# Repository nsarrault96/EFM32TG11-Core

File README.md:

# Kicad Project Template

This is a simple kicad project template designed to use submodules for any additional pieces including libraries,
firmware/software and CAD design.

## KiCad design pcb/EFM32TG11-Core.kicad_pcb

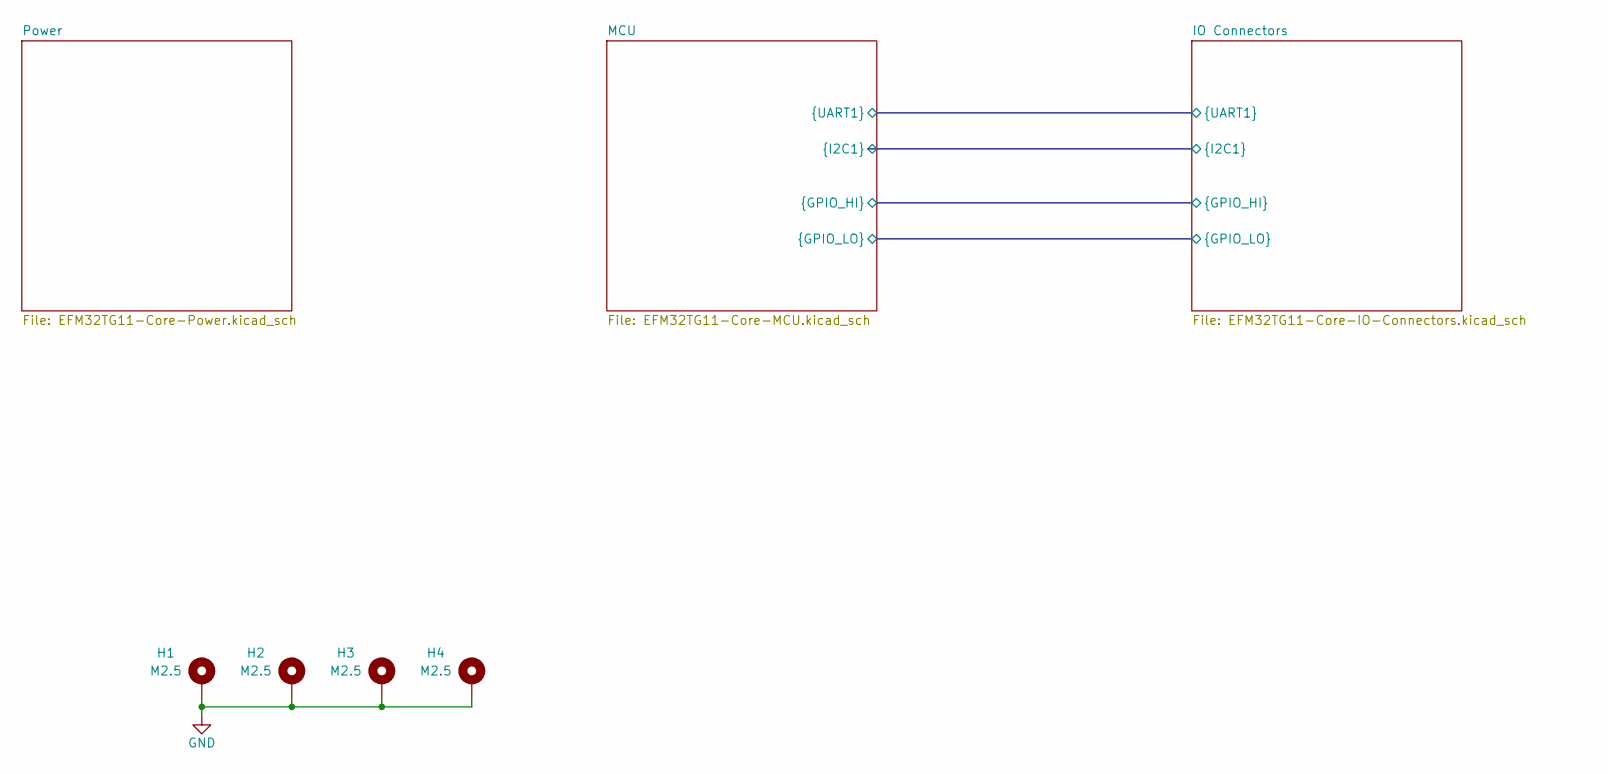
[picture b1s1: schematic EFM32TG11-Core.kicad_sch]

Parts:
H1, H2, H3, H4: M2.5; MountingHole_2.7mm_M2.5_Pad

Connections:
GND: H1.1, H2.1, H3.1, H4.1; also elsewhere on the board

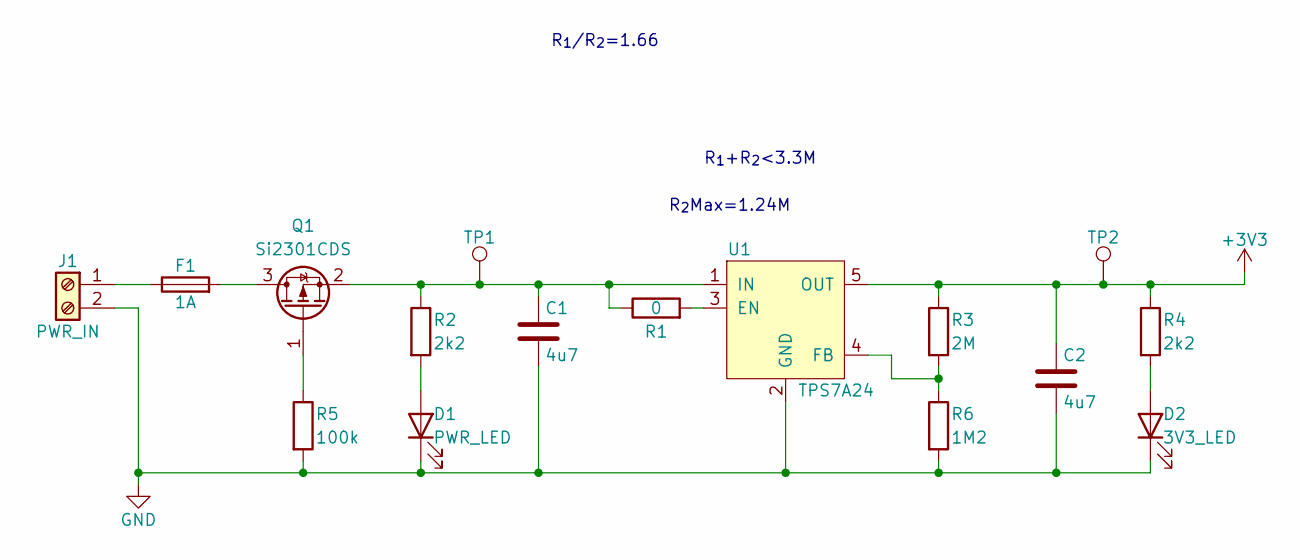
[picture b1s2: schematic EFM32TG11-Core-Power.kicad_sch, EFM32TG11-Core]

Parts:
C1, C2: 4u7; C_0805_2012Metric; PartsBox PN CAP-0805-4u7-X7R-25V
D1: PWR_LED; D_0603_1608Metric_Pad1.05x0.95mm_HandSolder; PartsBox PN LTST-C191KRKT
D2: 3V3_LED; D_0603_1608Metric_Pad1.05x0.95mm_HandSolder; PartsBox PN LTST-C191KRKT
F1: 1A; Fuse_0603_1608Metric; PartsBox PN 0686F1000-01
J1: PWR_IN; TerminalBlock_Phoenix_PT-1,5-2-3.5-H_1x02_P3.50mm_Horizontal; PartsBox PN 1984617
Q1: Si2301CDS; SOT-23; PartsBox PN SI2301CDS-T1-GE3
R1: 0; R_0603_1608Metric; PartsBox PN RES-0603-0R-0.1W
R2, R4: 2k2; R_0603_1608Metric; PartsBox PN RES-0603-2k2-0.1W
R3: 2M; R_0603_1608Metric; PartsBox PN RES-0603-2M-0.1W
R5: 100k; R_0603_1608Metric; PartsBox PN RES-0603-100k-0.1W
R6: 1M2; R_0603_1608Metric; PartsBox PN RES-0603-1M2-0.1W
TP1, TP2: TestPoint; TestPoint_Pad_D1.0mm
U1: TPS7A24; SOT-23-5; PartsBox PN TPS7A2401DBVR

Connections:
+3V3: C2.1, R3.1, R4.1, TP2.1, U1.5 (OUT); also elsewhere on the board
GND: C1.2, C2.2, D1.1 (K), D2.1 (K), J1.2, R5.2, R6.2, U1.2 (GND); also elsewhere on the board
unnamed: C1.1, Q1.2 (S), R1.1, R2.1, TP1.1, U1.1 (IN)
unnamed: D1.2 (A), R2.2
unnamed: D2.2 (A), R4.2
unnamed: F1.1, J1.1
unnamed: F1.2, Q1.3 (D)
unnamed: Q1.1 (G), R5.1
unnamed: R1.2, U1.3 (EN)
unnamed: R3.2, R6.1, U1.4 (FB)

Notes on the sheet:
R_{2}Max=1.24M
R_{1}/R_{2}=1.66
R_{1}+R_{2}<3.3M

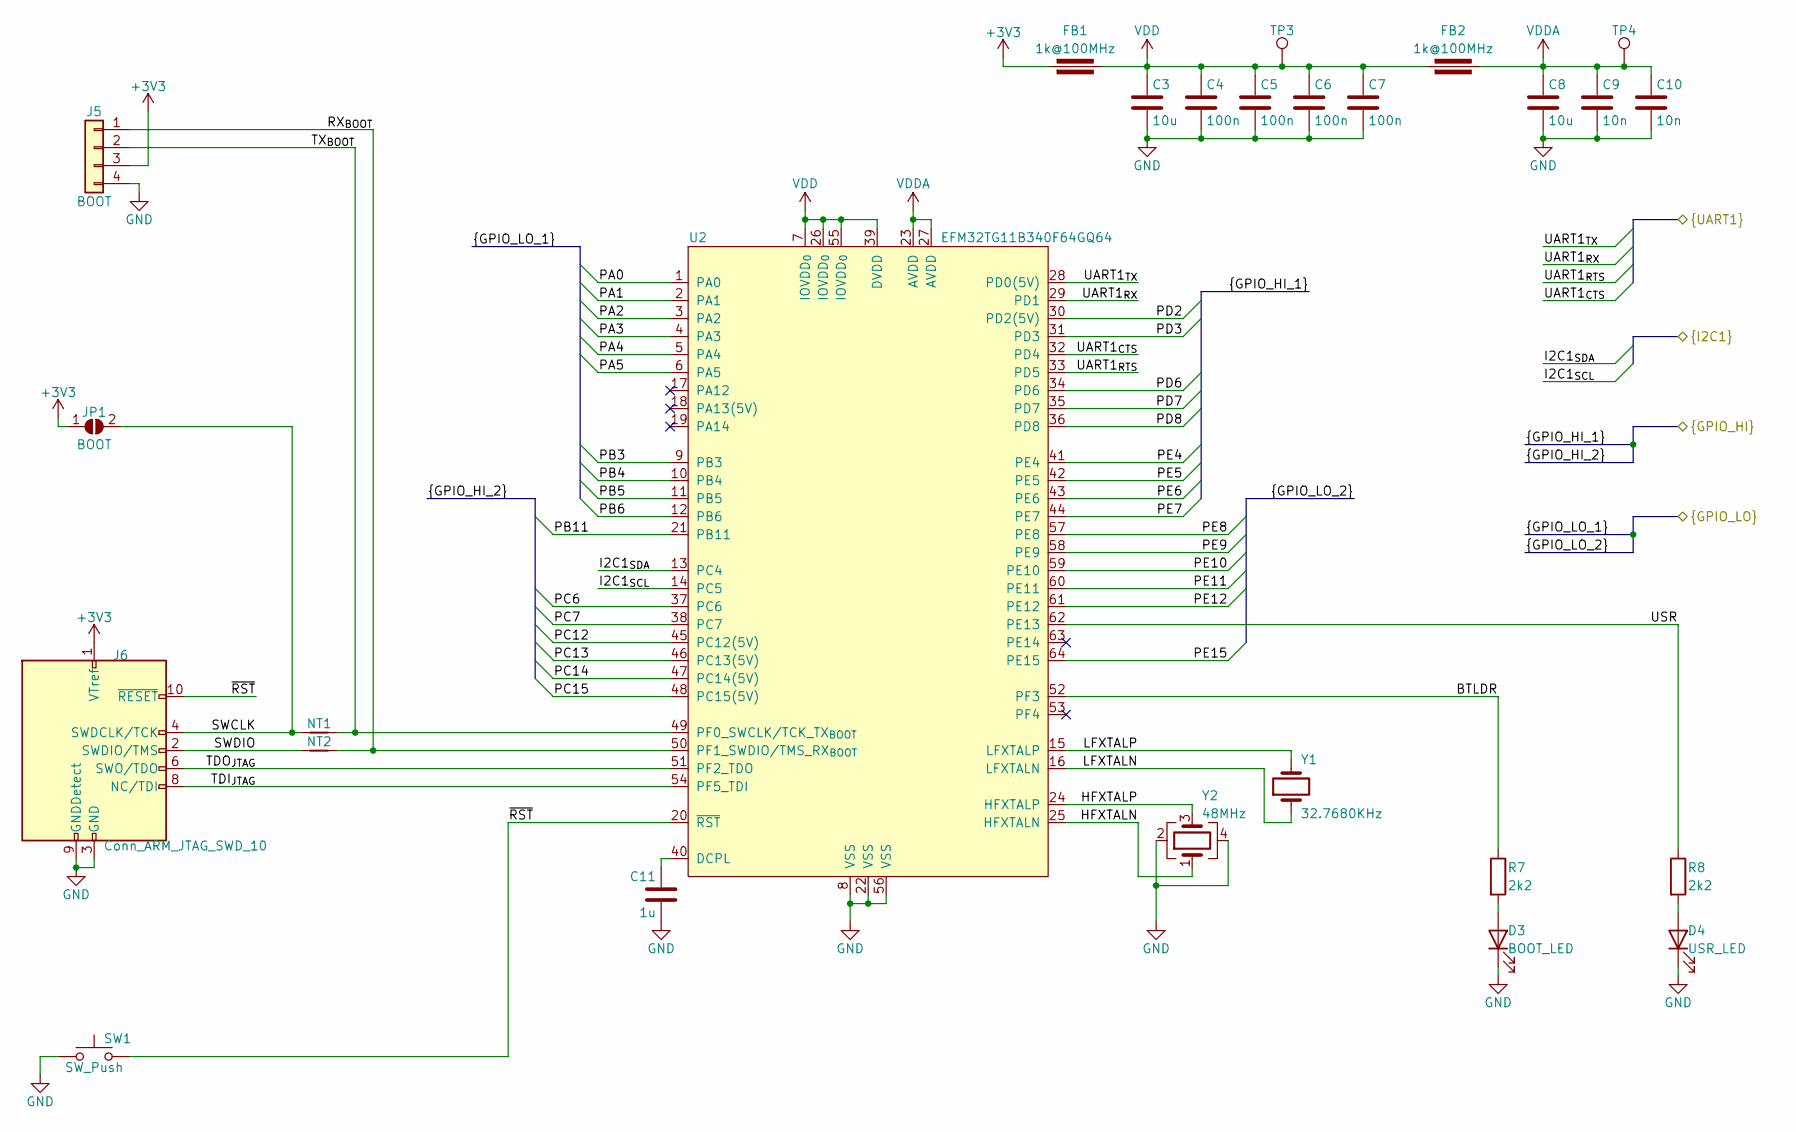
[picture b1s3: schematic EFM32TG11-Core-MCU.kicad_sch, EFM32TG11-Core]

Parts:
C3, C8: 10u; C_1206_3216Metric; PartsBox PN CAP-1206-10u-X7R-25V
C4, C5, C6, C7: 100n; C_0603_1608Metric; PartsBox PN CAP-0603-100n-X7R-50V
C9, C10: 10n; C_0603_1608Metric; PartsBox PN CAP-0603-10n-X7R-50V
C11: 1u; C_0603_1608Metric; PartsBox PN CAP-0603-1u-X7R-25V
D3: BOOT_LED; D_0603_1608Metric_Pad1.05x0.95mm_HandSolder; PartsBox PN LTST-C191KFKT
D4: USR_LED; D_0603_1608Metric_Pad1.05x0.95mm_HandSolder; PartsBox PN LTST-C191KFKT
FB1, FB2: 1k@100MHz; L_0603_1608Metric; PartsBox PN BLM18KG102SN1D
J5: BOOT; PinHeader_1x04_P2.54mm_Horizontal
J6: Conn_ARM_JTAG_SWD_10; PinHeader_2x05_P1.27mm_Vertical
JP1: BOOT; SolderJumper-2_P1.3mm_Open_RoundedPad1.0x1.5mm
NT1, NT2: NetTie_2; NetTie-2_THT_Pad0.3mm
R7, R8: 2k2; R_0603_1608Metric; PartsBox PN RES-0603-2k2-0.1W
SW1: SW_Push; SW_SPST_CK_RS282G05A3; PartsBox PN TS-1101-C-W
TP3, TP4: TestPoint; TestPoint_Pad_D1.0mm
U2: EFM32TG11B340F64GQ64; TQFP-64_10x10mm_P0.5mm; PartsBox PN EFM32TG11B340F64GQ64-A
Y1: 32.7680KHz; Crystal_SMD_MicroCrystal_CC7V-T1A-2Pin_3.2x1.5mm; PartsBox PN FC-135 32.7680KA-AG5
Y2: 48MHz; Crystal_SMD_2016-4Pin_2.0x1.6mm; PartsBox PN 7D048000I01

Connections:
+3V3: FB1.1, J5.3, J6.1 (VTref), JP1.1 (A); also elsewhere on the board
/IO Connectors/UART1_{CTS}: U2.32 (PD4); also elsewhere on the board
/IO Connectors/UART1_{RTS}: U2.33 (PD5); also elsewhere on the board
/IO Connectors/UART1_{RX}: U2.29 (PD1); also elsewhere on the board
/IO Connectors/UART1_{TX}: U2.28 (PD0(5V)); also elsewhere on the board
/MCU/BTLDR: R7.1, U2.52 (PF3)
/MCU/HFXTALN: U2.25 (HFXTALN), Y2.1
/MCU/HFXTALP: U2.24 (HFXTALP), Y2.3
/MCU/I2C1_{SCL}: U2.14 (PC5)
/MCU/I2C1_{SDA}: U2.13 (PC4)
/MCU/LFXTALN: U2.16 (LFXTALN), Y1.1
/MCU/LFXTALP: U2.15 (LFXTALP), Y1.2
/MCU/PA0: U2.1 (PA0)
/MCU/PA1: U2.2 (PA1)
/MCU/PA2: U2.3 (PA2)
/MCU/PA3: U2.4 (PA3)
/MCU/PA4: U2.5 (PA4)
/MCU/PA5: U2.6 (PA5)
/MCU/PB3: U2.9 (PB3)
/MCU/PB4: U2.10 (PB4)
/MCU/PB5: U2.11 (PB5)
/MCU/PB6: U2.12 (PB6)
/MCU/PB11: U2.21 (PB11)
/MCU/PC6: U2.37 (PC6)
/MCU/PC7: U2.38 (PC7)
/MCU/PC12: U2.45 (PC12(5V))
/MCU/PC13: U2.46 (PC13(5V))
/MCU/PC14: U2.47 (PC14(5V))
/MCU/PC15: U2.48 (PC15(5V))
/MCU/PD2: U2.30 (PD2(5V))
/MCU/PD3: U2.31 (PD3)
/MCU/PD6: U2.34 (PD6)
/MCU/PD7: U2.35 (PD7)
/MCU/PD8: U2.36 (PD8)
/MCU/PE4: U2.41 (PE4)
/MCU/PE5: U2.42 (PE5)
/MCU/PE6: U2.43 (PE6)
/MCU/PE7: U2.44 (PE7)
/MCU/PE8: U2.57 (PE8)
/MCU/PE9: U2.58 (PE9)
/MCU/PE10: U2.59 (PE10)
/MCU/PE11: U2.60 (PE11)
/MCU/PE12: U2.61 (PE12)
/MCU/PE15: U2.64 (PE15)
/MCU/RX_{BOOT}: J5.1, NT2.2, U2.50 (PF1_SWDIO/TMS_RX_{BOOT})
/MCU/SWCLK: J6.4 (SWDCLK/TCK), JP1.2 (B), NT1.1
/MCU/SWDIO: J6.2 (SWDIO/TMS), NT2.1
/MCU/TDI_{JTAG}: J6.8 (NC/TDI), U2.54 (PF5_TDI)
/MCU/TDO_{JTAG}: J6.6 (SWO/TDO), U2.51 (PF2_TDO)
/MCU/TX_{BOOT}: J5.2, NT1.2, U2.49 (PF0_SWCLK/TCK_TX_{BOOT})
/MCU/USR: R8.1, U2.62 (PE13)
/MCU/~RST: J6.10 (~RESET), SW1.2, U2.20 (~RST)
GND: C3.2, C4.2, C5.2, C6.2, C7.2, C8.2, C9.2, C10.2, C11.2, D3.1 (K), D4.1 (K), J5.4, J6.3 (GND), J6.5 (GND), J6.9 (GNDDetect), SW1.1, U2.8 (VSS), U2.22 (VSS), U2.56 (VSS), Y2.2, Y2.4; also elsewhere on the board
unnamed: C11.1, U2.40 (DCPL)
unnamed: D3.2 (A), R7.2
unnamed: D4.2 (A), R8.2
VDD: C3.1, C4.1, C5.1, C6.1, C7.1, FB1.2, FB2.1, TP3.1, U2.7 (IOVDD_{0}), U2.26 (IOVDD_{0}), U2.39 (DVDD), U2.55 (IOVDD_{0})
VDDA: C8.1, C9.1, C10.1, FB2.2, TP4.1, U2.23 (AVDD), U2.27 (AVDD)

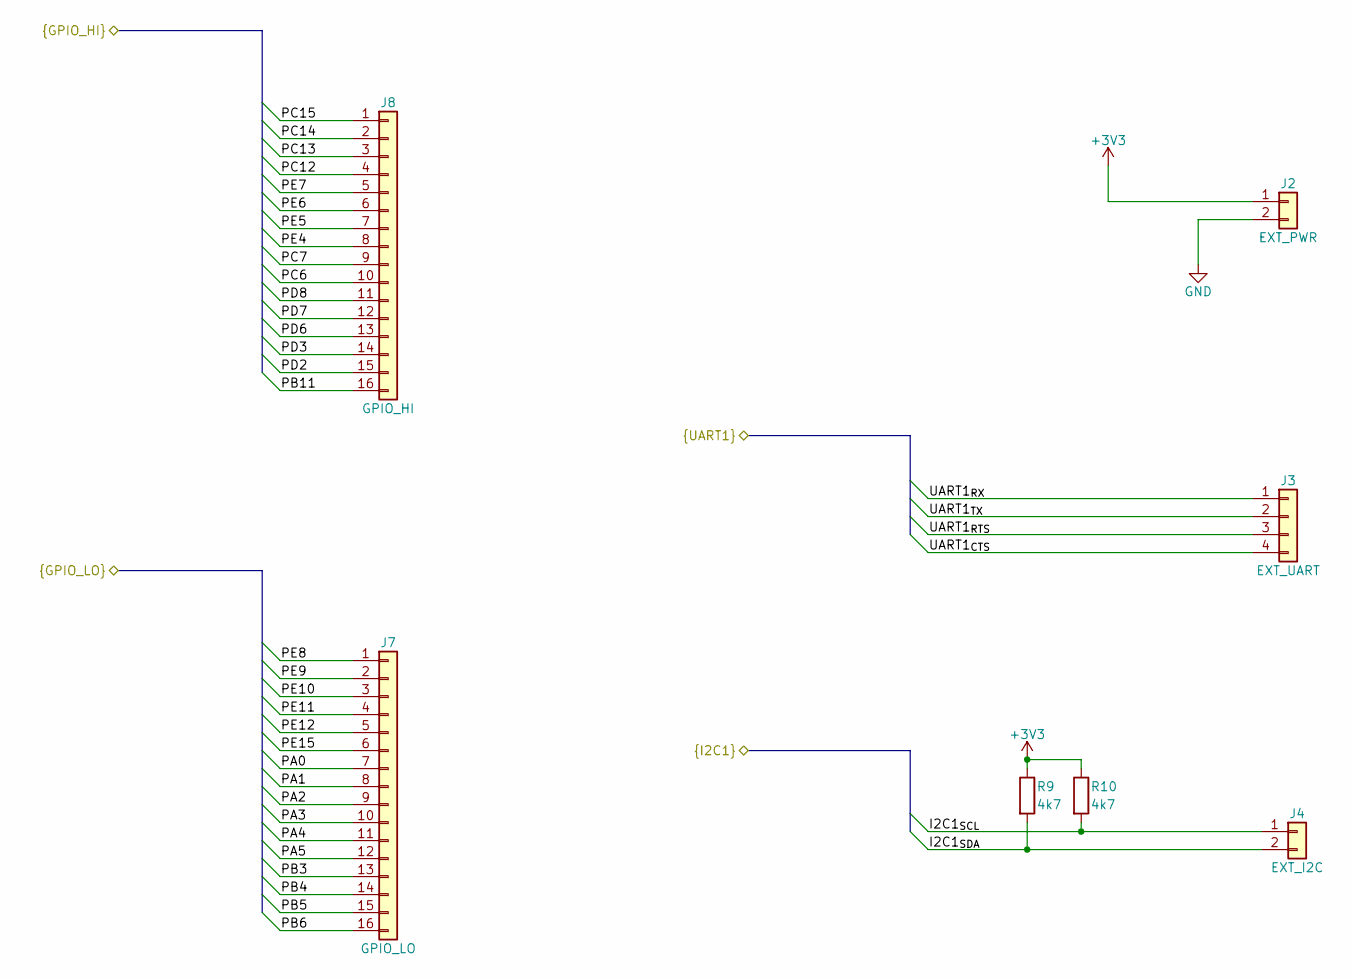
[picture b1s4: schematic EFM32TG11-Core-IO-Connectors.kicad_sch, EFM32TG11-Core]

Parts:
J2: EXT_PWR; PinHeader_1x02_P2.54mm_Horizontal
J3: EXT_UART; PinHeader_1x04_P2.54mm_Horizontal
J4: EXT_I2C; PinHeader_1x02_P2.54mm_Horizontal
J7: GPIO_LO; PinSocket_1x16_P2.54mm_Vertical
J8: GPIO_HI; PinSocket_1x16_P2.54mm_Vertical
R9, R10: 4k7; R_0603_1608Metric; PartsBox PN RES-0603-4k7-0.1W

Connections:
+3V3: J2.1, R9.1, R10.1; also elsewhere on the board
/IO Connectors/I2C1_{SCL}: J4.1, R10.2
/IO Connectors/I2C1_{SDA}: J4.2, R9.2
/IO Connectors/PA0: J7.7
/IO Connectors/PA1: J7.8
/IO Connectors/PA2: J7.9
/IO Connectors/PA3: J7.10
/IO Connectors/PA4: J7.11
/IO Connectors/PA5: J7.12
/IO Connectors/PB3: J7.13
/IO Connectors/PB4: J7.14
/IO Connectors/PB5: J7.15
/IO Connectors/PB6: J7.16
/IO Connectors/PB11: J8.16
/IO Connectors/PC6: J8.10
/IO Connectors/PC7: J8.9
/IO Connectors/PC12: J8.4
/IO Connectors/PC13: J8.3
/IO Connectors/PC14: J8.2
/IO Connectors/PC15: J8.1
/IO Connectors/PD2: J8.15
/IO Connectors/PD3: J8.14
/IO Connectors/PD6: J8.13
/IO Connectors/PD7: J8.12
/IO Connectors/PD8: J8.11
/IO Connectors/PE4: J8.8
/IO Connectors/PE5: J8.7
/IO Connectors/PE6: J8.6
/IO Connectors/PE7: J8.5
/IO Connectors/PE8: J7.1
/IO Connectors/PE9: J7.2
/IO Connectors/PE10: J7.3
/IO Connectors/PE11: J7.4
/IO Connectors/PE12: J7.5
/IO Connectors/PE15: J7.6
/IO Connectors/UART1_{CTS}: J3.4; also elsewhere on the board
/IO Connectors/UART1_{RTS}: J3.3; also elsewhere on the board
/IO Connectors/UART1_{RX}: J3.1; also elsewhere on the board
/IO Connectors/UART1_{TX}: J3.2; also elsewhere on the board
GND: J2.2; also elsewhere on the board

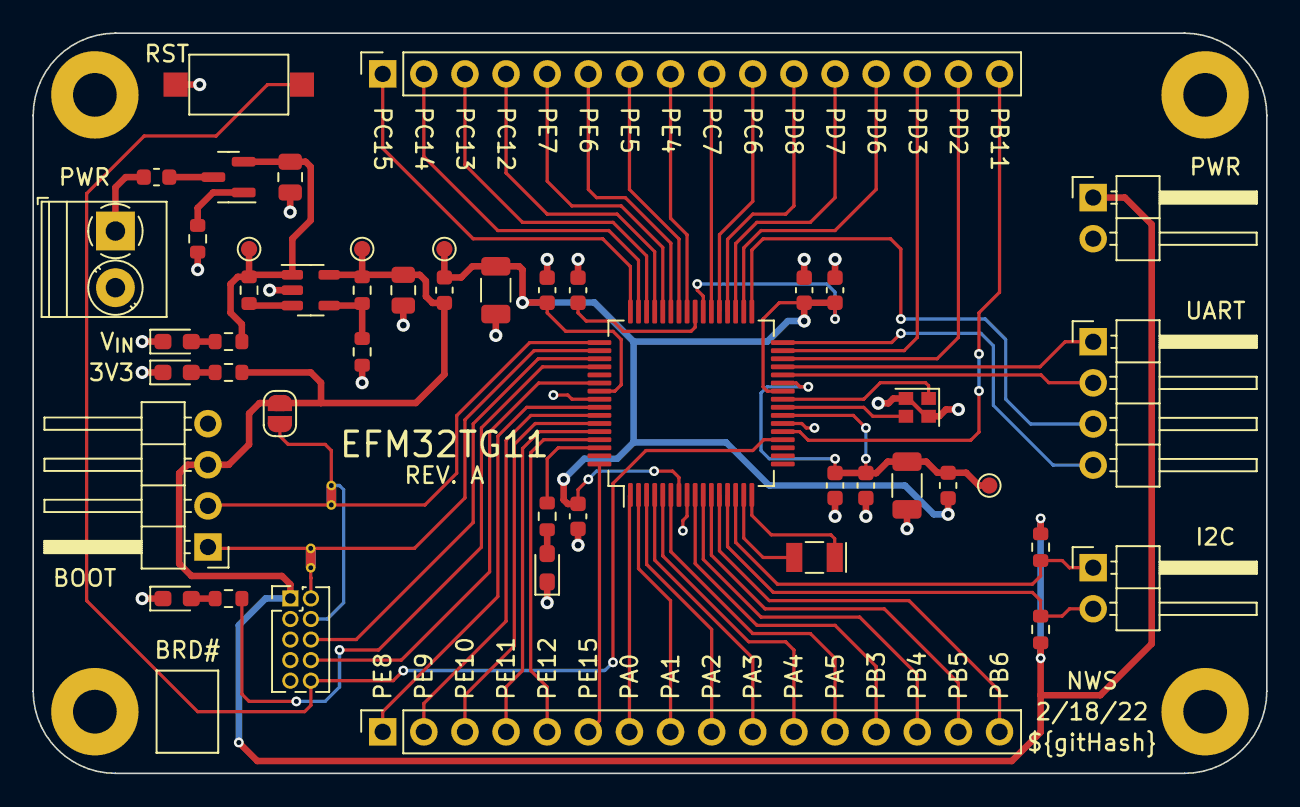
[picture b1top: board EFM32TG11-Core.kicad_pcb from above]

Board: 2 copper layers, 76.2 x 45.7 mm, 53 parts (0 on the bottom side), 34 nets.

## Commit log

2022-02-23 Initial Commit
    Initial commit of the project with revision A of the schematic and
    PCB. As sent to OSHPark on 2/18/2022.
2022-02-24 Reorganization of schematic to heirarchical sheets
    Took single sheet schematic and reorganized to 3 heirarchical sheets.
    This allowed for the schematic to be printable on 8.5"x11" sheets of
    paper without losing clarity of the schematic. All reference
    designators were maintained.
    Buses and interconnects between pages still need to be added to the
    schematic to finish transition.
2022-02-24 Fix Nets for Hierarchical Sheets
    Defined busses to pass nets to and from MCU sheet and IO connector
    sheet.
2022-02-25 Added commit hash to schematic and PCB
    Commit hash was added as a text variable to be added to the schematic
    title block and the PCB silkscreen layer. A box with label to record
    the board # was also added to the PCB silkscreen layer.
    [Issue: X]
2022-02-25 Update clean script for project
    Updated the clean filter to ignore the hash in the project file.
    This allows me to stay up to date with the hash. Otherwise it
    would always be behind.
